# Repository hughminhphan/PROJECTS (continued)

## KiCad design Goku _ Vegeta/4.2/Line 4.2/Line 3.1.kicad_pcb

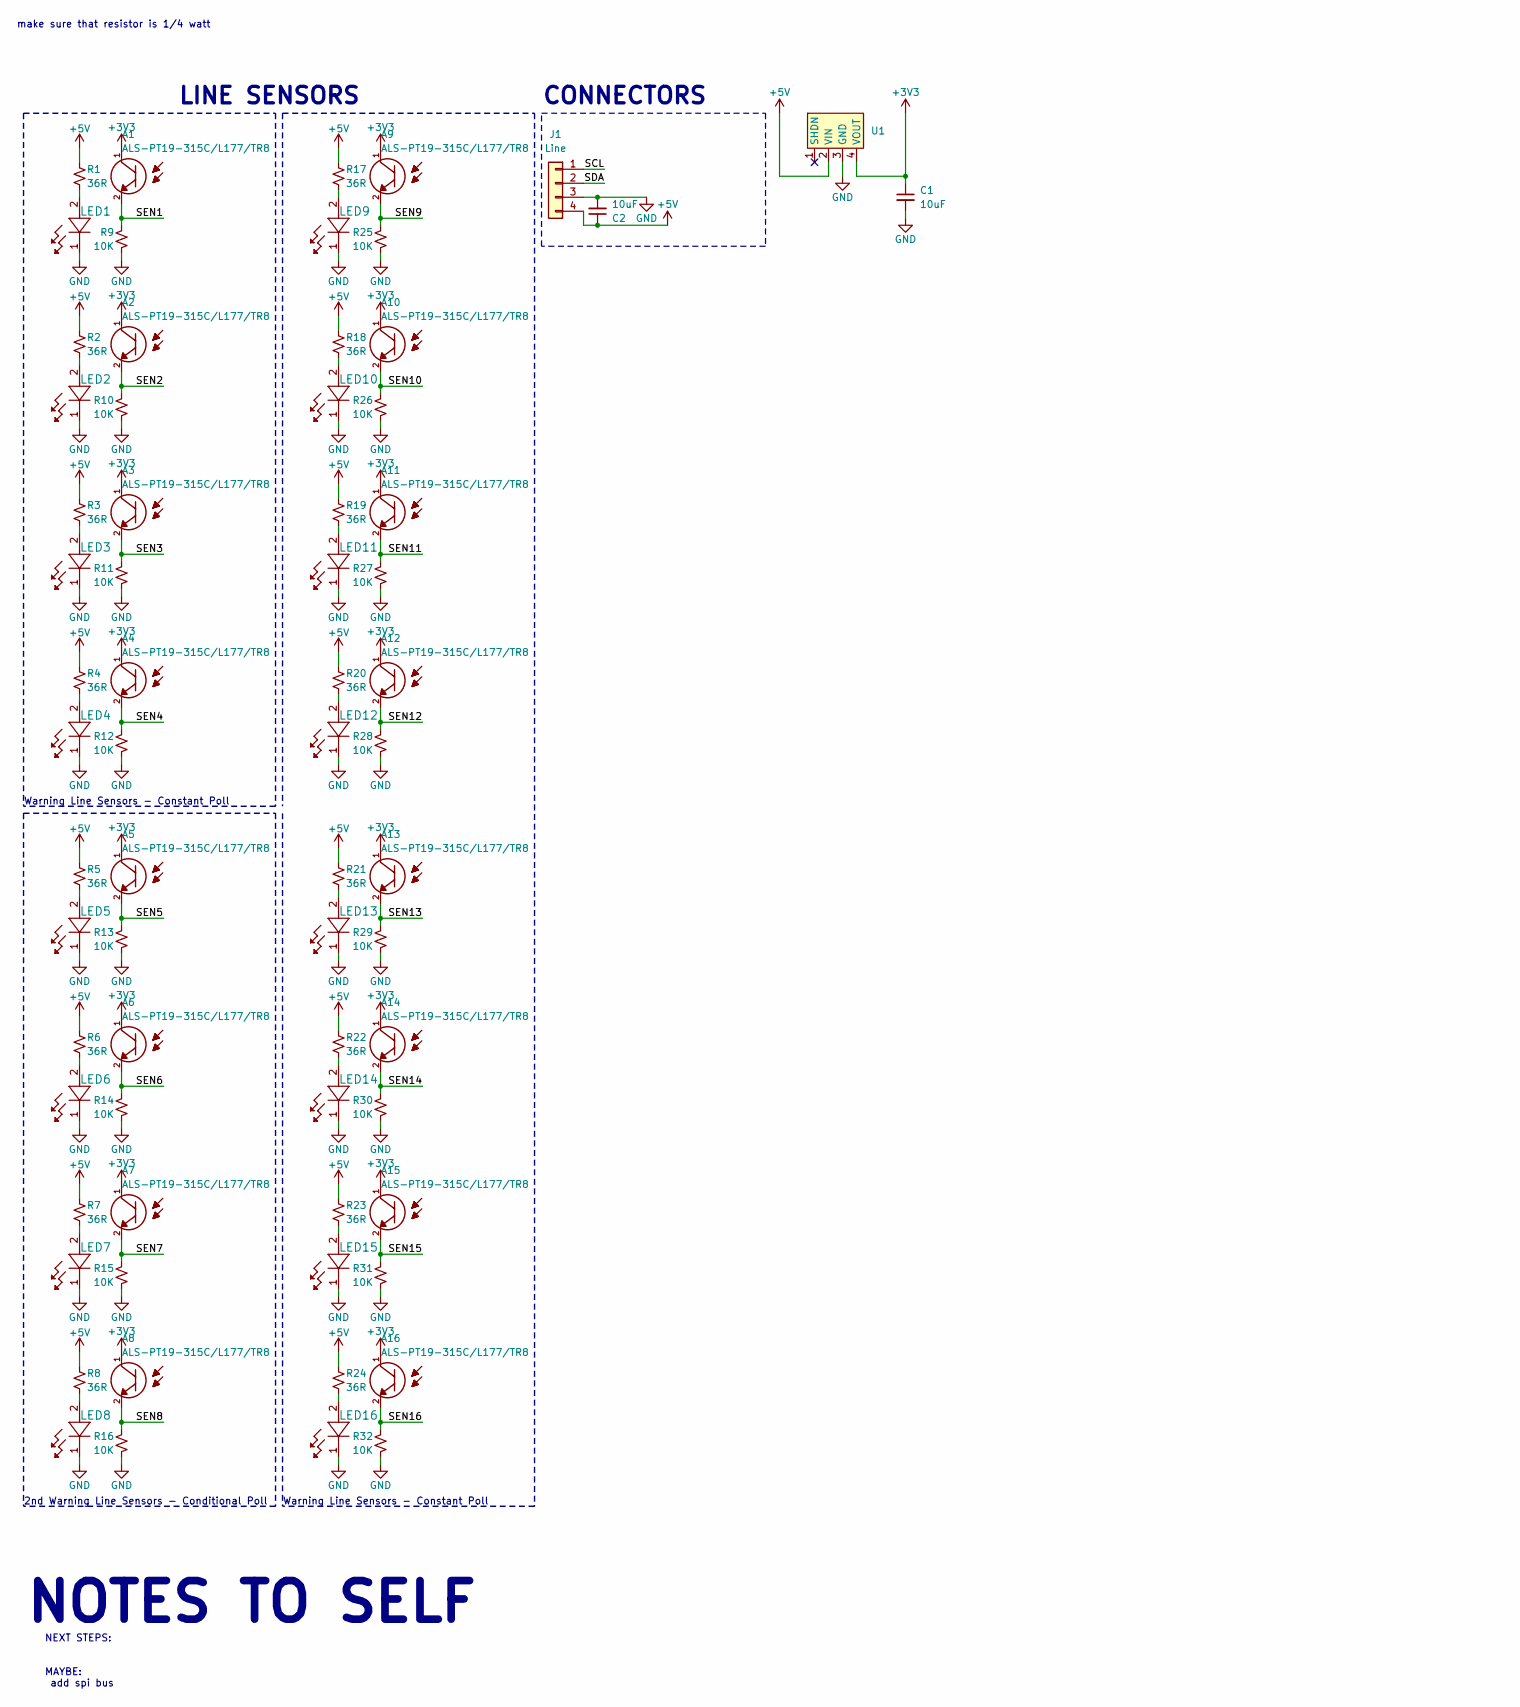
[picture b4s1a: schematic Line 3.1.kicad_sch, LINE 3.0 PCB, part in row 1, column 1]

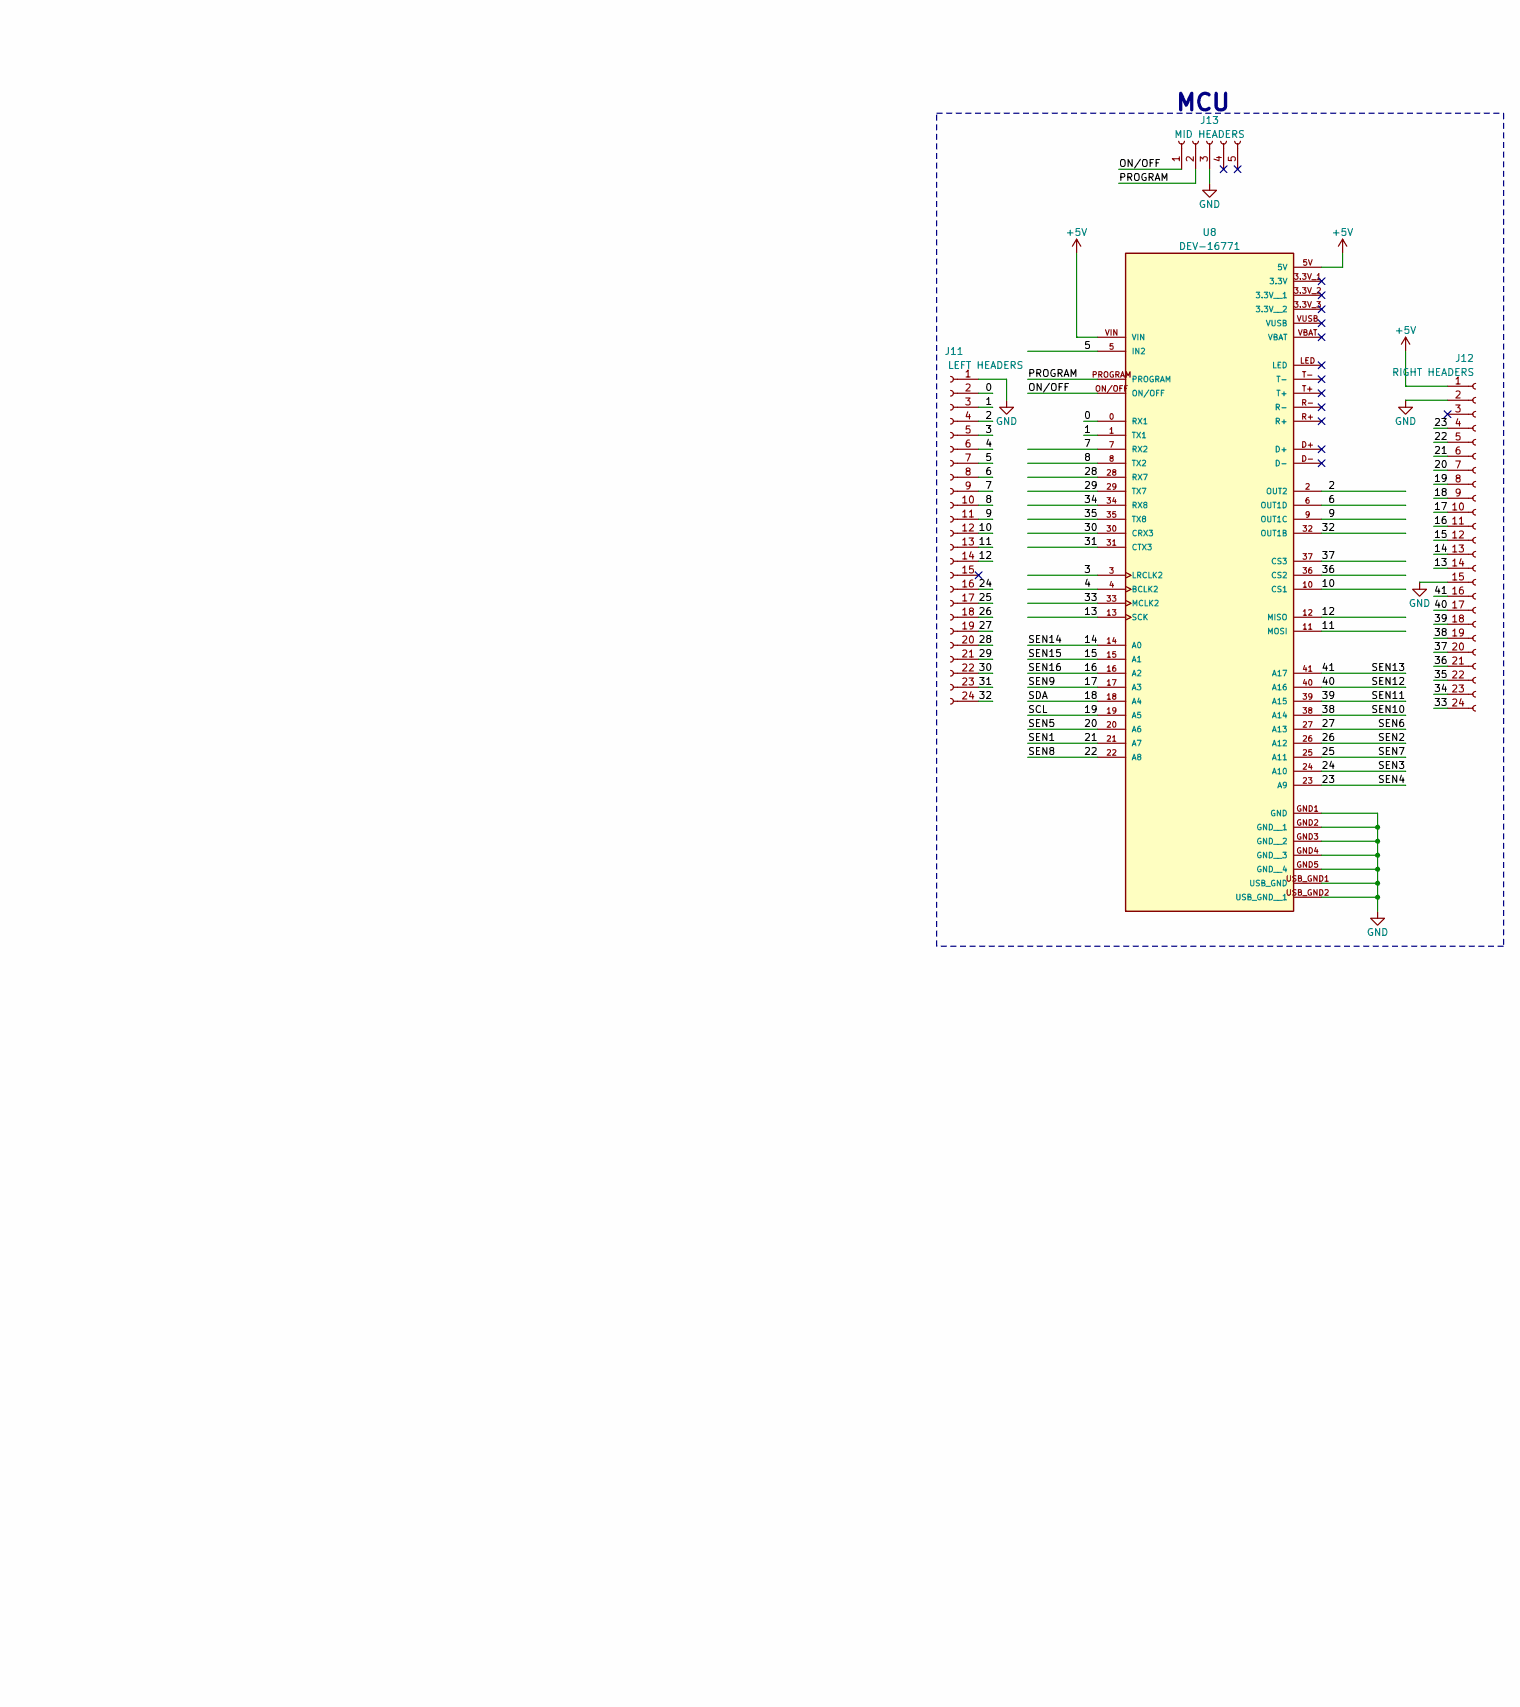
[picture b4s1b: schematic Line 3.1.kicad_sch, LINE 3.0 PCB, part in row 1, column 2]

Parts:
A1, A2, A3, A4, A5, A6, A7, A8, A9, A10, A11, A12, A13, A14, A15, A16: ALS-PT19-315C/L177/TR8; XDCR_ALS-PT19-315C_L177_TR8; PARTREV 5
C1, C2: 10uF; C_0805_2012Metric
J1: Line; JST_XH_B4B-XH-A_1x04_P2.50mm_Vertical
J11: LEFT HEADERS; PinSocket_1x24_P2.54mm_Vertical
J12: RIGHT HEADERS; PinSocket_1x24_P2.54mm_Vertical
J13: MID HEADERS; PinSocket_1x05_P2.54mm_Vertical
LED1, LED2, LED3, LED4, LED5, LED6, LED7, LED8, LED9, LED10, LED11, LED12, LED13, LED14, LED15, LED16: JB2835AWT-W-U30GA0000-N0000001; LED_J2835_CRW
R1, R2, R3, R4, R5, R6, R7, R8, R17, R18, R19, R20, R21, R22, R23, R24: 36R; R_0805_2012Metric
R9, R10, R11, R12, R13, R14, R15, R16, R25, R26, R27, R28, R29, R30, R31, R32: 10K; R_0805_2012Metric
U1: Pololu 3.3V, 500mA Step-Down Voltage Regulator D24V5F3
U8: DEV-16771; MODULE_DEV-16771; PARTREV 4.1

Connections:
+3V3: A1.1, A2.1, A3.1, A4.1, A5.1, A6.1, A7.1, A8.1, A9.1, A10.1, A11.1, A12.1, A13.1, A14.1, A15.1, A16.1, C1.1, U1.4 (VOUT)
+5V: C2.1, J1.4, J12.1, R1.1, R2.1, R3.1, R4.1, R5.1, R6.1, R7.1, R8.1, R17.1, R18.1, R19.1, R20.1, R21.1, R22.1, R23.1, R24.1, U1.2 (VIN), U8.5V, U8.VIN
/0: J11.2, U8.0 (RX1)
/1: J11.3, U8.1 (TX1)
/2: J11.4, U8.2 (OUT2)
/3: J11.5, U8.3 (LRCLK2)
/4: J11.6, U8.4 (BCLK2)
/5: J11.7, U8.5 (IN2)
/6: J11.8, U8.6 (OUT1D)
/7: J11.9, U8.7 (RX2)
/8: J11.10, U8.8 (TX2)
/9: J11.11, U8.9 (OUT1C)
/10: J11.12, U8.10 (CS1)
/11: J11.13, U8.11 (MOSI)
/12: J11.14, U8.12 (MISO)
/13: J12.14, U8.13 (SCK)
/14: A14.2, J12.13, R30.2, U8.14 (A0)
/15: A15.2, J12.12, R31.2, U8.15 (A1)
/16: A16.2, J12.11, R32.2, U8.16 (A2)
/17: A9.2, J12.10, R25.2, U8.17 (A3)
/18: J1.2, J12.9, U8.18 (A4)
/19: J1.1, J12.8, U8.19 (A5)
/20: A5.2, J12.7, R13.2, U8.20 (A6)
/21: A1.2, J12.6, R9.2, U8.21 (A7)
/22: A8.2, J12.5, R16.2, U8.22 (A8)
/23: A4.2, J12.4, R12.2, U8.23 (A9)
/24: A3.2, J11.16, R11.2, U8.24 (A10)
/25: A7.2, J11.17, R15.2, U8.25 (A11)
/26: A2.2, J11.18, R10.2, U8.26 (A12)
/27: A6.2, J11.19, R14.2, U8.27 (A13)
/28: J11.20, U8.28 (RX7)
/29: J11.21, U8.29 (TX7)
/30: J11.22, U8.30 (CRX3)
/31: J11.23, U8.31 (CTX3)
/32: J11.24, U8.32 (OUT1B)
/33: J12.24, U8.33 (MCLK2)
/34: J12.23, U8.34 (RX8)
/35: J12.22, U8.35 (TX8)
/36: J12.21, U8.36 (CS2)
/37: J12.20, U8.37 (CS3)
/38: A10.2, J12.19, R26.2, U8.38 (A14)
/39: A11.2, J12.18, R27.2, U8.39 (A15)
/40: A12.2, J12.17, R28.2, U8.40 (A16)
/41: A13.2, J12.16, R29.2, U8.41 (A17)
/ON/OFF: J13.1, U8.ON/OFF
/PROGRAM: J13.2, U8.PROGRAM
GND: C1.2, C2.2, J1.3, J11.1, J12.2, J12.15, J13.3, LED1.1, LED2.1, LED3.1, LED4.1, LED5.1, LED6.1, LED7.1, LED8.1, LED9.1, LED10.1, LED11.1, LED12.1, LED13.1, LED14.1, LED15.1, LED16.1, R9.1, R10.1, R11.1, R12.1, R13.1, R14.1, R15.1, R16.1, R25.1, R26.1, R27.1, R28.1, R29.1, R30.1, R31.1, R32.1, U1.3 (GND), U8.GND1 (GND), U8.GND2 (GND__1), U8.GND3 (GND__2), U8.GND4 (GND__3), U8.GND5 (GND__4), U8.USB_GND1 (USB_GND), U8.USB_GND2 (USB_GND__1)
unnamed: LED1.2, R1.2
unnamed: LED2.2, R2.2
unnamed: LED3.2, R3.2
unnamed: LED4.2, R4.2
unnamed: LED5.2, R5.2
unnamed: LED6.2, R6.2
unnamed: LED7.2, R7.2
unnamed: LED8.2, R8.2
unnamed: LED9.2, R17.2
unnamed: LED10.2, R18.2
unnamed: LED11.2, R19.2
unnamed: LED12.2, R20.2
unnamed: LED13.2, R21.2
unnamed: LED14.2, R22.2
unnamed: LED15.2, R23.2
unnamed: LED16.2, R24.2

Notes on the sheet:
NOTES TO SELF
NEXT STEPS: MAYBE: add spi bus
CONNECTORS
LINE SENSORS
2nd Warning Line Sensors - Conditional Poll
make sure that resistor is 1/4 watt
Warning Line Sensors - Constant Poll
MCU

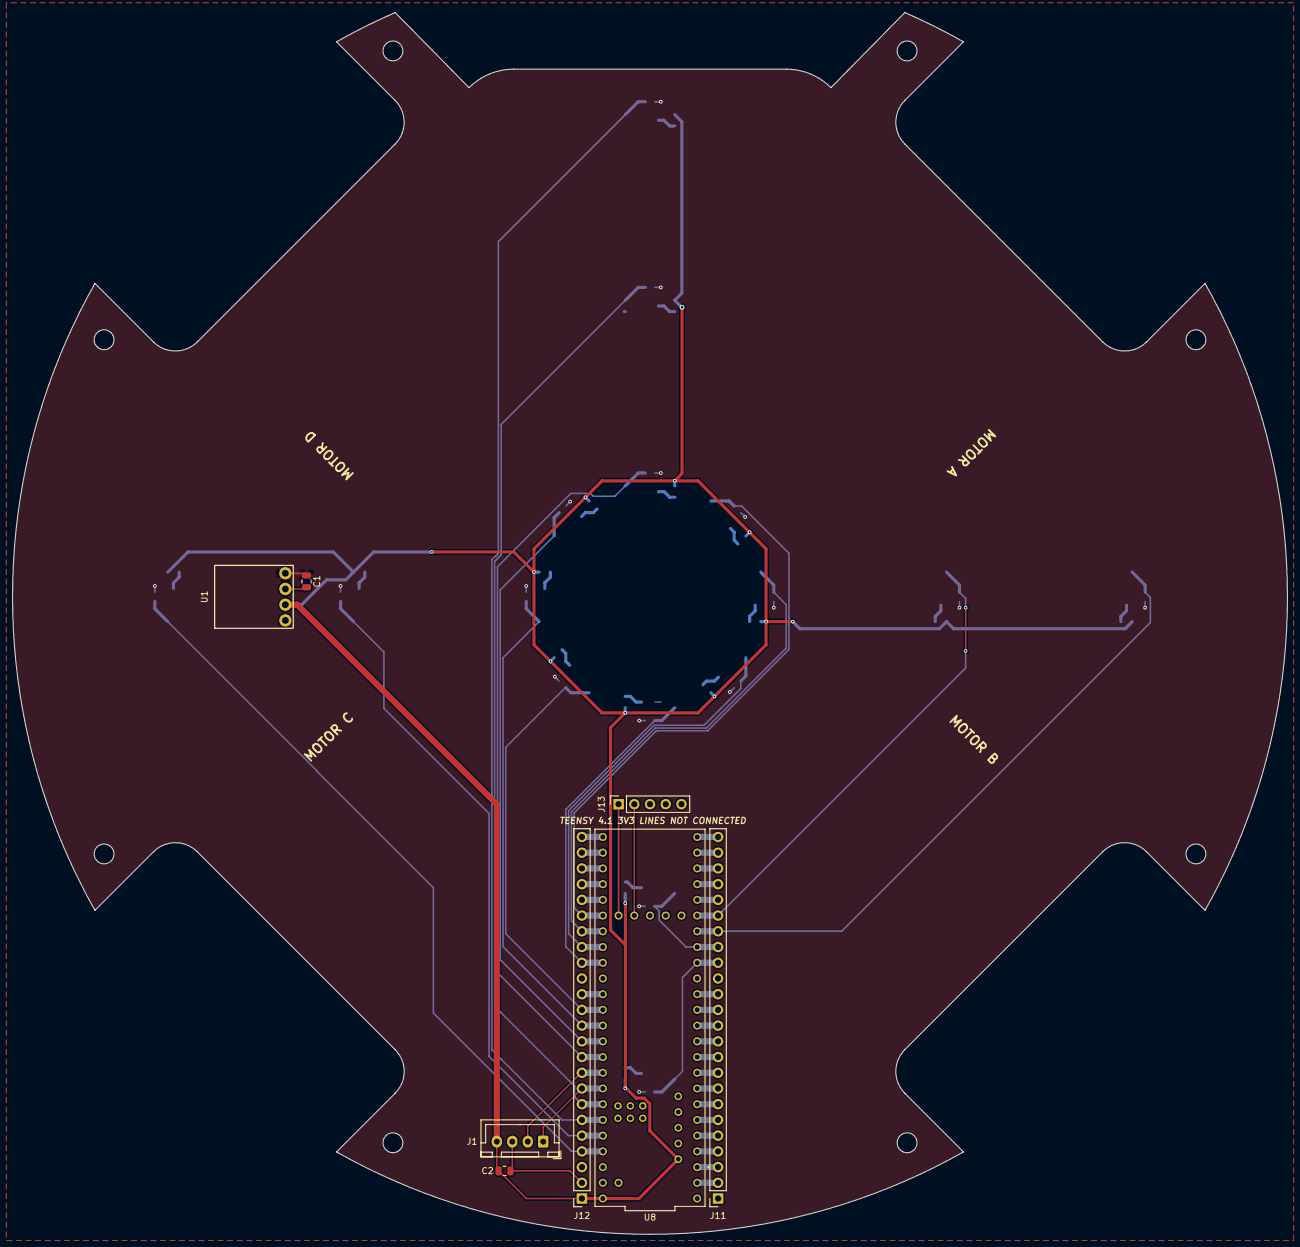
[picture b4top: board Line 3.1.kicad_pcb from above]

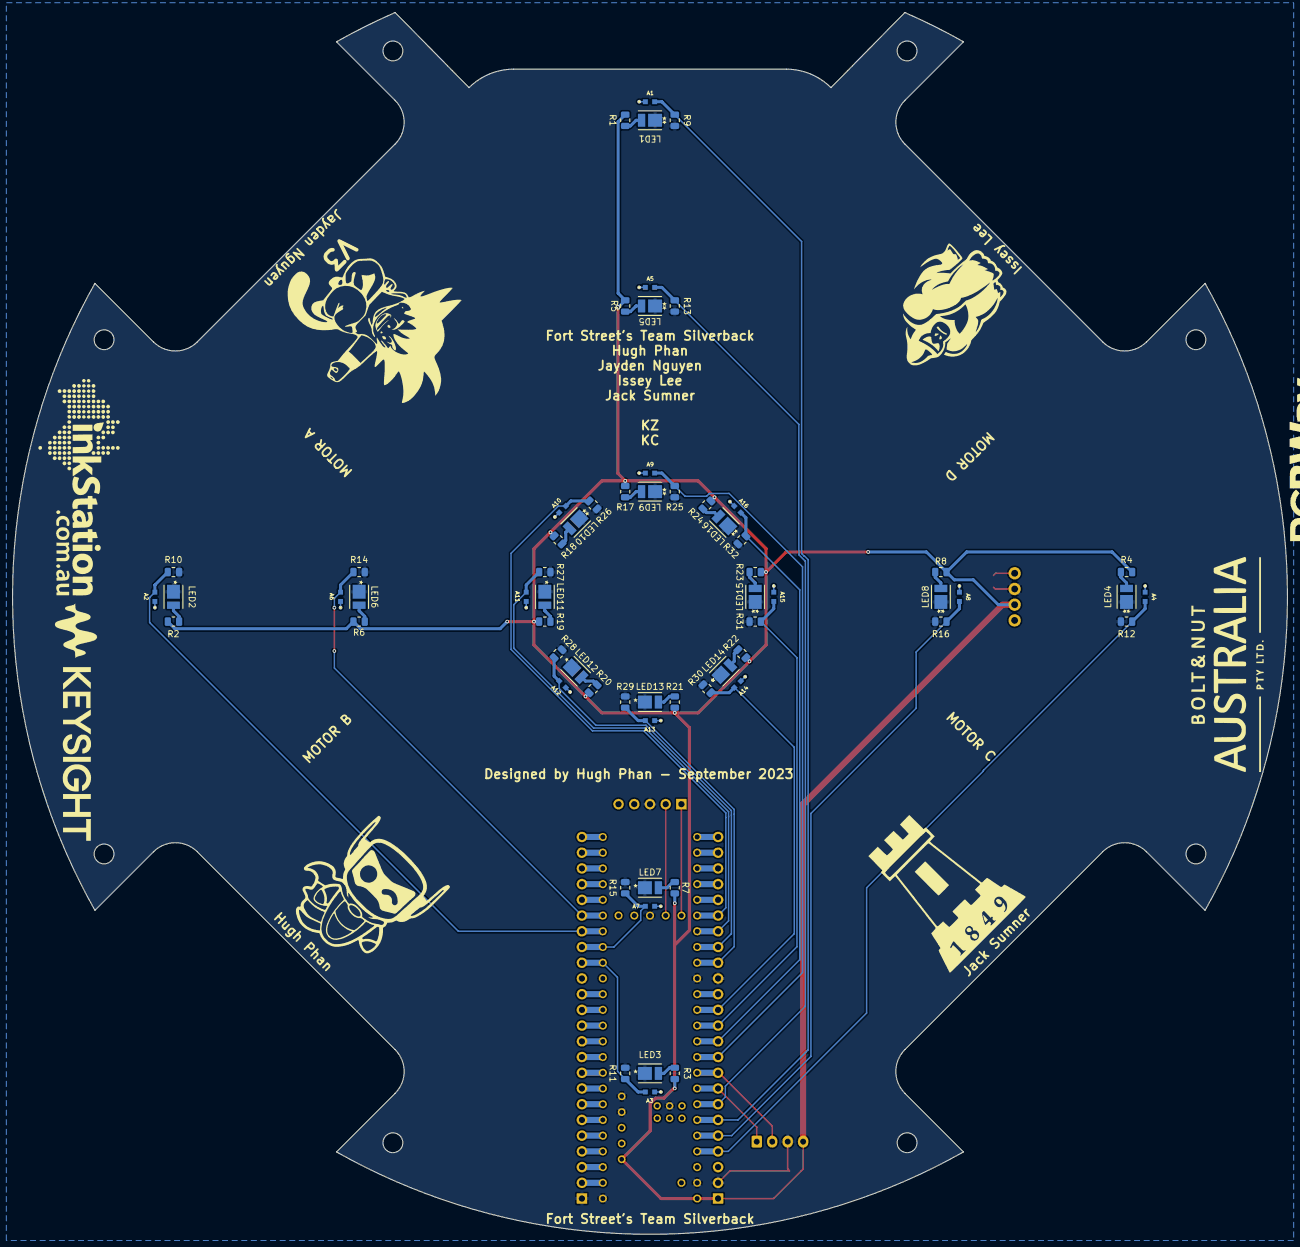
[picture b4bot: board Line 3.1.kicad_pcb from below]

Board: 2 copper layers, 206.0 x 197.4 mm, 72 parts (64 on the bottom side), 63 nets.

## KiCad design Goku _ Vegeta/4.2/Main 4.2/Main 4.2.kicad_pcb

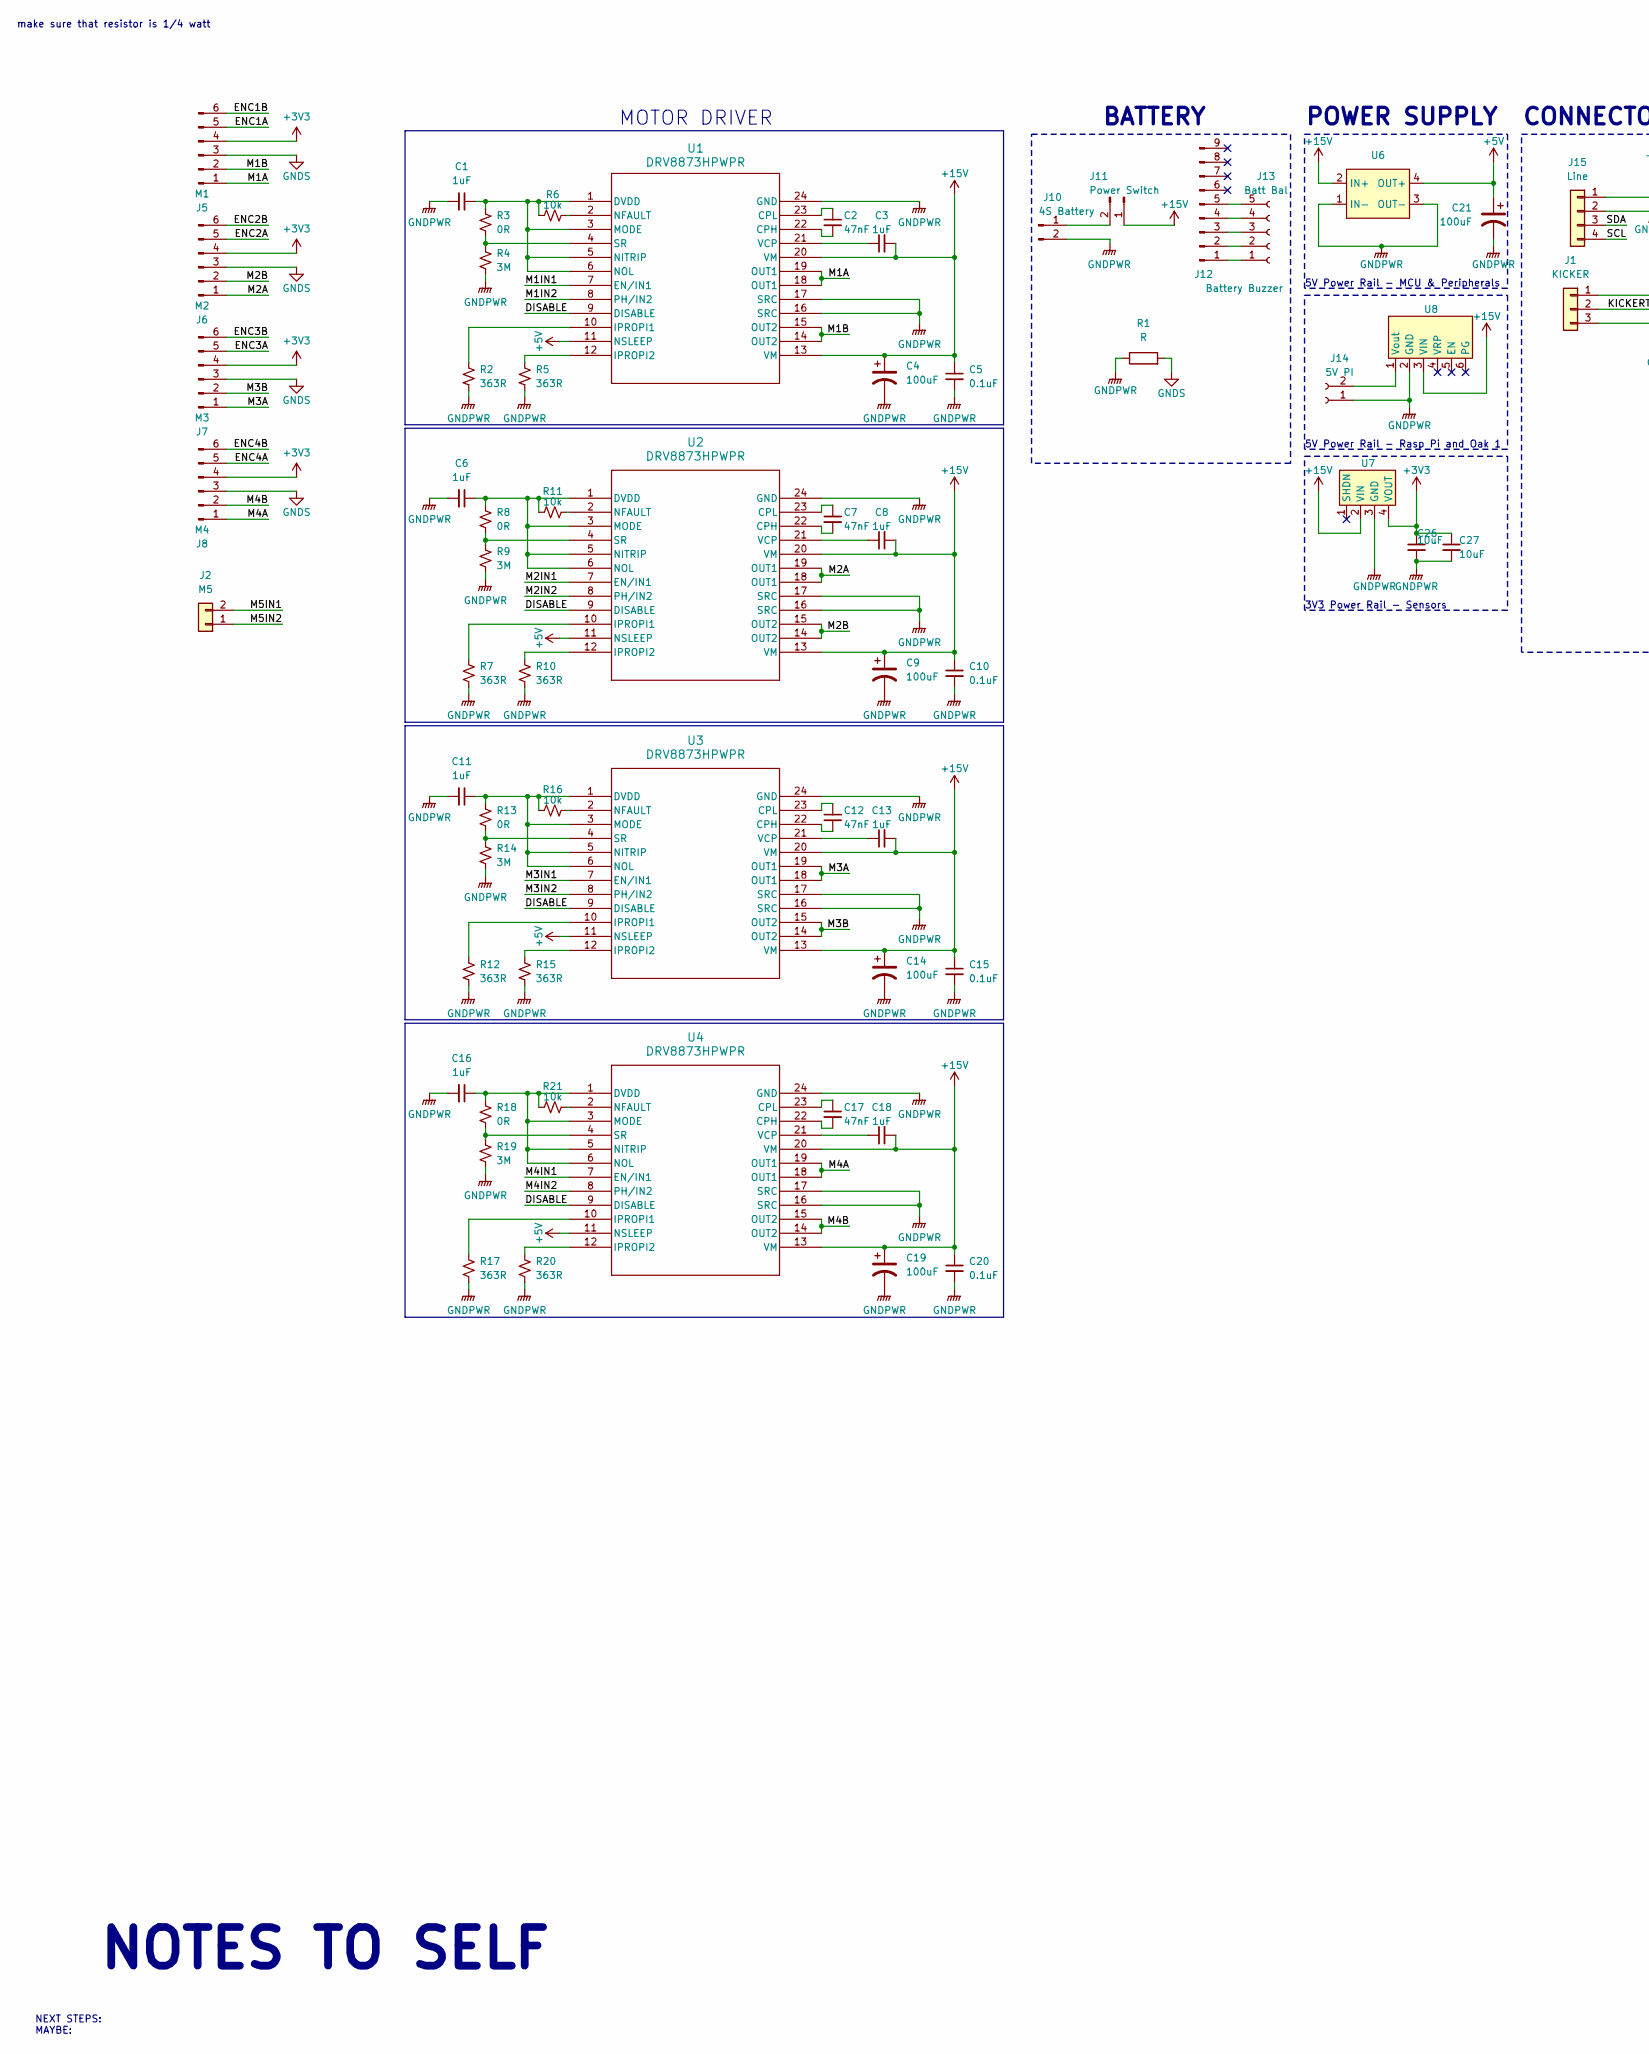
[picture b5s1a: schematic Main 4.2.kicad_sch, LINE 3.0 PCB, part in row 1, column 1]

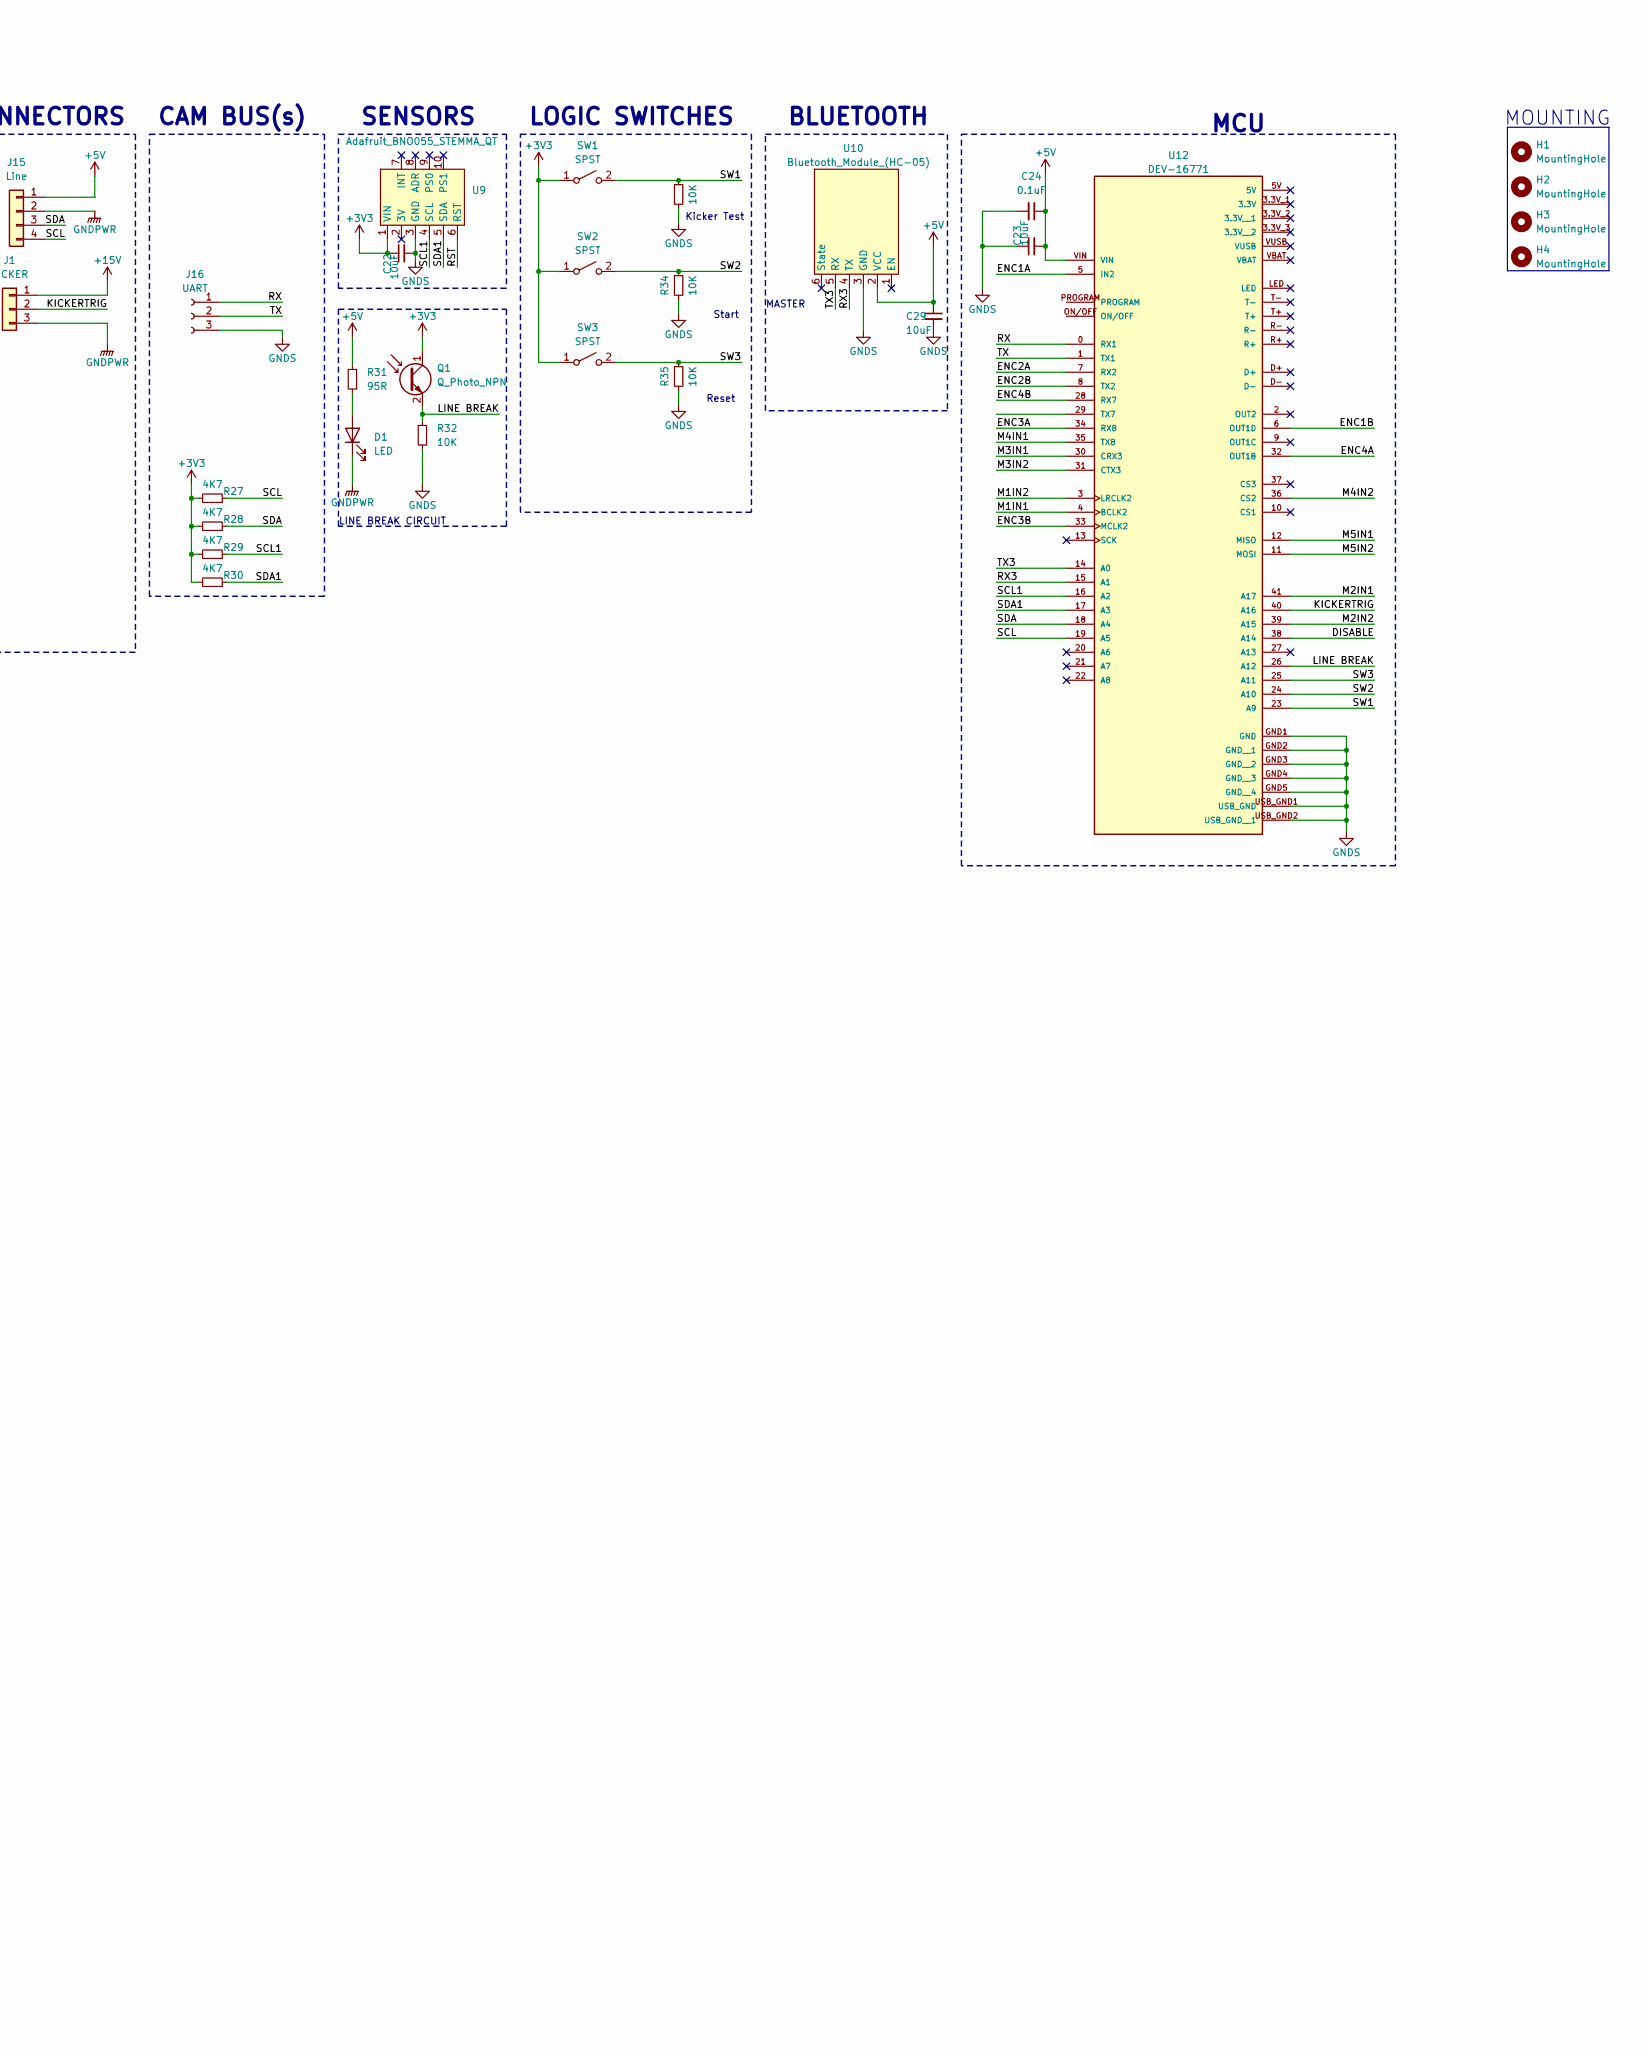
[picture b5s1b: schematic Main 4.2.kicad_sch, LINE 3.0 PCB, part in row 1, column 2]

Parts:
C1, C3, C6, C8, C11, C13, C16, C18: 1uF; C_0402_1005Metric
C2, C7, C12, C17: 47nF; C_0402_1005Metric
C4, C9, C14, C19, C21: 100uF; CP_Elec_6.3x7.7
C5, C10, C15, C20, C24: 0.1uF; C_0402_1005Metric
C22, C23, C26, C27, C29: 10uF; C_0805_2012Metric
D1: LED; LED_D3.0mm
H1, H2, H3, H4: MountingHole; MountingHole_3.2mm_M3
J1: KICKER; JST_XH_B3B-XH-A_1x03_P2.50mm_Vertical
J2: M5; PinHeader_1x02_P2.54mm_Vertical
J5: M1; PinHeader_1x06_P2.54mm_Vertical
J6: M2; PinHeader_1x06_P2.54mm_Vertical
J7: M3; PinHeader_1x06_P2.54mm_Vertical
J8: M4; PinHeader_1x06_P2.54mm_Vertical
J10: 4S Battery; AMASS_XT30U-F_1x02_P5.0mm_Vertical
J11: Power Switch; AMASS_XT30U-M_1x02_P5.0mm_Vertical
J12: Battery Buzzer; PinHeader_1x09_P2.54mm_Vertical
J13: Batt Bal; JST_XH_B5B-XH-A_1x05_P2.50mm_Vertical
J14: 5V PI; SolderWire-0.75sqmm_1x02_P4.8mm_D1.25mm_OD2.3mm
J15: Line; JST_XH_B4B-XH-A_1x04_P2.50mm_Vertical
J16: UART; PinSocket_1x03_P2.54mm_Vertical
Q1: Q_Photo_NPN; LED_D3.0mm
R1: R; R_1210_3225Metric
R2, R5, R7, R10, R12, R15, R17, R20: 363R; R_0805_2012Metric
R3, R8, R13, R18: 0R; R_0805_2012Metric
R4, R9, R14, R19: 3M; R_0805_2012Metric
R6, R11, R16, R21: 10k; R_0402_1005Metric
R27, R28, R29, R30: 4K7; R_0805_2012Metric
R31: 95R; R_0805_2012Metric
R32, R33, R34, R35: 10K; R_0805_2012Metric
SW1, SW2, SW3: SPST; SW_PUSH_6mm_H4.3mm
U1, U2, U3, U4: DRV8873HPWPR; PWP24_TEX
U6: DC-DC Multi-output Buck Converter
U7: Pololu 3.3V, 500mA Step-Down Voltage Regulator D24V5F3
U8: 5V, 5.5A Step-Down Voltage Regulator D36V50F5
U9: Adafruit_BNO055_STEMMA_QT; Adafruit IMU BNO055
U10: Bluetooth_Module_(HC-05); PinHeader_1x06_P2.54mm_Vertical
U12: DEV-16771; MODULE_DEV-16771; PARTREV 4.1

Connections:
+3V3: C22.1, C26.1, C27.1, J5.4, J6.4, J7.4, J8.4, Q1.1 (C), R27.2, R28.2, R29.2, R30.2, SW1.1 (A), SW2.1 (A), SW3.1 (A), U7.4 (VOUT), U9.1 (VIN)
+5V: C21.1, C23.2, C24.1, C29.1, J15.1, R31.1, U1.11 (NSLEEP), U2.11 (NSLEEP), U3.11 (NSLEEP), U4.11 (NSLEEP), U6.4 (OUT+), U10.2 (VCC), U12.VIN
+15V: C3.2, C4.1, C5.1, C8.2, C9.1, C10.1, C13.2, C14.1, C15.1, C18.2, C19.1, C20.1, J1.1, J11.1, U1.13 (VM), U1.20 (VM), U2.13 (VM), U2.20 (VM), U3.13 (VM), U3.20 (VM), U4.13 (VM), U4.20 (VM), U6.2 (IN+), U7.2 (VIN), U8.3 (VIN)
/DISABLE: U1.9 (DISABLE), U2.9 (DISABLE), U3.9 (DISABLE), U4.9 (DISABLE), U12.38 (A14)
/ENC1A: J5.5, U12.5 (IN2)
/ENC1B: J5.6, U12.6 (OUT1D)
/ENC2A: J6.5, U12.7 (RX2)
/ENC2B: J6.6, U12.8 (TX2)
/ENC3A: J7.5, U12.34 (RX8)
/ENC3B: J7.6, U12.33 (MCLK2)
/ENC4A: J8.5, U12.32 (OUT1B)
/ENC4B: J8.6, U12.28 (RX7)
/KICKERTRIG: J1.2, U12.40 (A16)
/LINE BREAK: Q1.2 (E), R32.1, U12.26 (A12)
/M1A: J5.1, U1.18 (OUT1), U1.19 (OUT1)
/M1B: J5.2, U1.14 (OUT2), U1.15 (OUT2)
/M1IN1: U1.7 (EN/IN1), U12.4 (BCLK2)
/M1IN2: U1.8 (PH/IN2), U12.3 (LRCLK2)
/M2A: J6.1, U2.18 (OUT1), U2.19 (OUT1)
/M2B: J6.2, U2.14 (OUT2), U2.15 (OUT2)
/M2IN1: U2.7 (EN/IN1), U12.41 (A17)
/M2IN2: U2.8 (PH/IN2), U12.39 (A15)
/M3A: J7.1, U3.18 (OUT1), U3.19 (OUT1)
/M3B: J7.2, U3.14 (OUT2), U3.15 (OUT2)
/M3IN1: U3.7 (EN/IN1), U12.30 (CRX3)
/M3IN2: U3.8 (PH/IN2), U12.31 (CTX3)
/M4A: J8.1, U4.18 (OUT1), U4.19 (OUT1)
/M4B: J8.2, U4.14 (OUT2), U4.15 (OUT2)
/M4IN1: U4.7 (EN/IN1), U12.35 (TX8)
/M4IN2: U4.8 (PH/IN2), U12.36 (CS2)
/M5IN1: J2.2, U12.12 (MISO)
/M5IN2: J2.1, U12.11 (MOSI)
/RST: U9.6 (RST)
/RX: J16.1, U12.0 (RX1)
/RX3: U10.4 (TX), U12.15 (A1)
/SCL: J15.4, R27.1, U12.19 (A5)
/SCL1: R29.1, U9.4 (SCL), U12.16 (A2)
/SDA: J15.3, R28.1, U12.18 (A4)
/SDA1: R30.1, U9.5 (SDA), U12.17 (A3)
/SW1: R33.1, SW1.2 (B), U12.23 (A9)
/SW2: R34.1, SW2.2 (B), U12.24 (A10)
/SW3: R35.1, SW3.2 (B), U12.25 (A11)
/TX: J16.2, U12.1 (TX1)
/TX3: U10.5 (RX), U12.14 (A0)
GNDPWR: C1.2, C4.2, C5.2, C6.2, C9.2, C10.2, C11.2, C14.2, C15.2, C16.2, C19.2, C20.2, C21.2, C26.2, C27.2, D1.1 (K), J1.3, J10.2, J14.1, J15.2, R1.1, R2.2, R4.2, R5.2, R7.2, R9.2, R10.2, R12.2, R14.2, R15.2, R17.2, R19.2, R20.2, U1.16 (SRC), U1.17 (SRC), U1.24 (GND), U1.EPAD, U2.16 (SRC), U2.17 (SRC), U2.24 (GND), U2.EPAD, U3.16 (SRC), U3.17 (SRC), U3.24 (GND), U3.EPAD, U4.16 (SRC), U4.17 (SRC), U4.24 (GND), U4.EPAD, U6.1 (IN-), U6.3 (OUT-), U7.3 (GND), U8.2 (GND)
GNDS: C22.2, C23.1, C24.2, C29.2, J5.3, J6.3, J7.3, J8.3, J16.3, R1.2, R32.2, R33.2, R34.2, R35.2, U9.3 (GND), U10.3 (GND), U12.GND1 (GND), U12.GND2 (GND__1), U12.GND3 (GND__2), U12.GND4 (GND__3), U12.GND5 (GND__4), U12.USB_GND1 (USB_GND), U12.USB_GND2 (USB_GND__1)
unnamed: D1.2 (A), R31.2
unnamed: J10.1, J11.2
unnamed: J12.1, J13.1
unnamed: J12.2, J13.2
unnamed: J12.3, J13.3
unnamed: J12.4, J13.4
unnamed: J12.5, J13.5
unnamed: J14.2, U8.1 (Vout)
unnamed: C2.2, U1.22 (CPH)
unnamed: C2.1, U1.23 (CPL)
unnamed: C1.1, R3.1, R6.1, U1.1 (DVDD), U1.3 (MODE), U1.5 (NITRIP), U1.6 (NOL)
unnamed: R2.1, U1.10 (IPROPI1)
unnamed: R5.1, U1.12 (IPROPI2)
unnamed: R6.2, U1.2 (NFAULT)
unnamed: R3.2, R4.1, U1.4 (SR)
unnamed: C3.1, U1.21 (VCP)
unnamed: C7.2, U2.22 (CPH)
unnamed: C7.1, U2.23 (CPL)
unnamed: C6.1, R8.1, R11.1, U2.1 (DVDD), U2.3 (MODE), U2.5 (NITRIP), U2.6 (NOL)
unnamed: R7.1, U2.10 (IPROPI1)
unnamed: R10.1, U2.12 (IPROPI2)
unnamed: R11.2, U2.2 (NFAULT)
unnamed: R8.2, R9.1, U2.4 (SR)
unnamed: C8.1, U2.21 (VCP)
unnamed: C12.2, U3.22 (CPH)
unnamed: C12.1, U3.23 (CPL)
unnamed: C11.1, R13.1, R16.1, U3.1 (DVDD), U3.3 (MODE), U3.5 (NITRIP), U3.6 (NOL)
unnamed: R12.1, U3.10 (IPROPI1)
unnamed: R15.1, U3.12 (IPROPI2)
unnamed: R16.2, U3.2 (NFAULT)
unnamed: R13.2, R14.1, U3.4 (SR)
unnamed: C13.1, U3.21 (VCP)
unnamed: C17.2, U4.22 (CPH)
unnamed: C17.1, U4.23 (CPL)
unnamed: C16.1, R18.1, R21.1, U4.1 (DVDD), U4.3 (MODE), U4.5 (NITRIP), U4.6 (NOL)
unnamed: R17.1, U4.10 (IPROPI1)
unnamed: R20.1, U4.12 (IPROPI2)
unnamed: R21.2, U4.2 (NFAULT)
unnamed: R18.2, R19.1, U4.4 (SR)
unnamed: C18.1, U4.21 (VCP)

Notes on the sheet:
NOTES TO SELF
MOUNTING
NEXT STEPS: MAYBE:
Kicker Test
CONNECTORS
MOTOR DRIVER
BATTERY
POWER SUPPLY
SENSORS
make sure that resistor is 1/4 watt
LINE BREAK CIRCUIT
5V Power Rail - Rasp Pi and Oak 1
MASTER
Start
Reset
LOGIC SWITCHES
BLUETOOTH
MCU
5V Power Rail - MCU & Peripherals
CAM BUS(s)
3V3 Power Rail - Sensors
